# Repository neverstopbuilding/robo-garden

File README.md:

#RoboGarden

An open source garden hacking project. A robot that will take care of my plants, because I can't. 

Blog posts relating to the development of this project can be found at [http://neverstopbuilding.net/blog/categories/robo-garden](http://neverstopbuilding.net/blog/categories/robo-garden)

##License
<br /><span xmlns:dct="http://purl.org/dc/terms/" property="dct:title">RoboGarden</span> by <span xmlns:cc="http://creativecommons.org/ns#" property="cc:attributionName">Jason Fox</span> is licensed under a <a rel="license" href="http://creativecommons.org/licenses/by-nc-sa/3.0/deed.en_US">Creative Commons Attribution-NonCommercial-ShareAlike 3.0 Unported License</a>.

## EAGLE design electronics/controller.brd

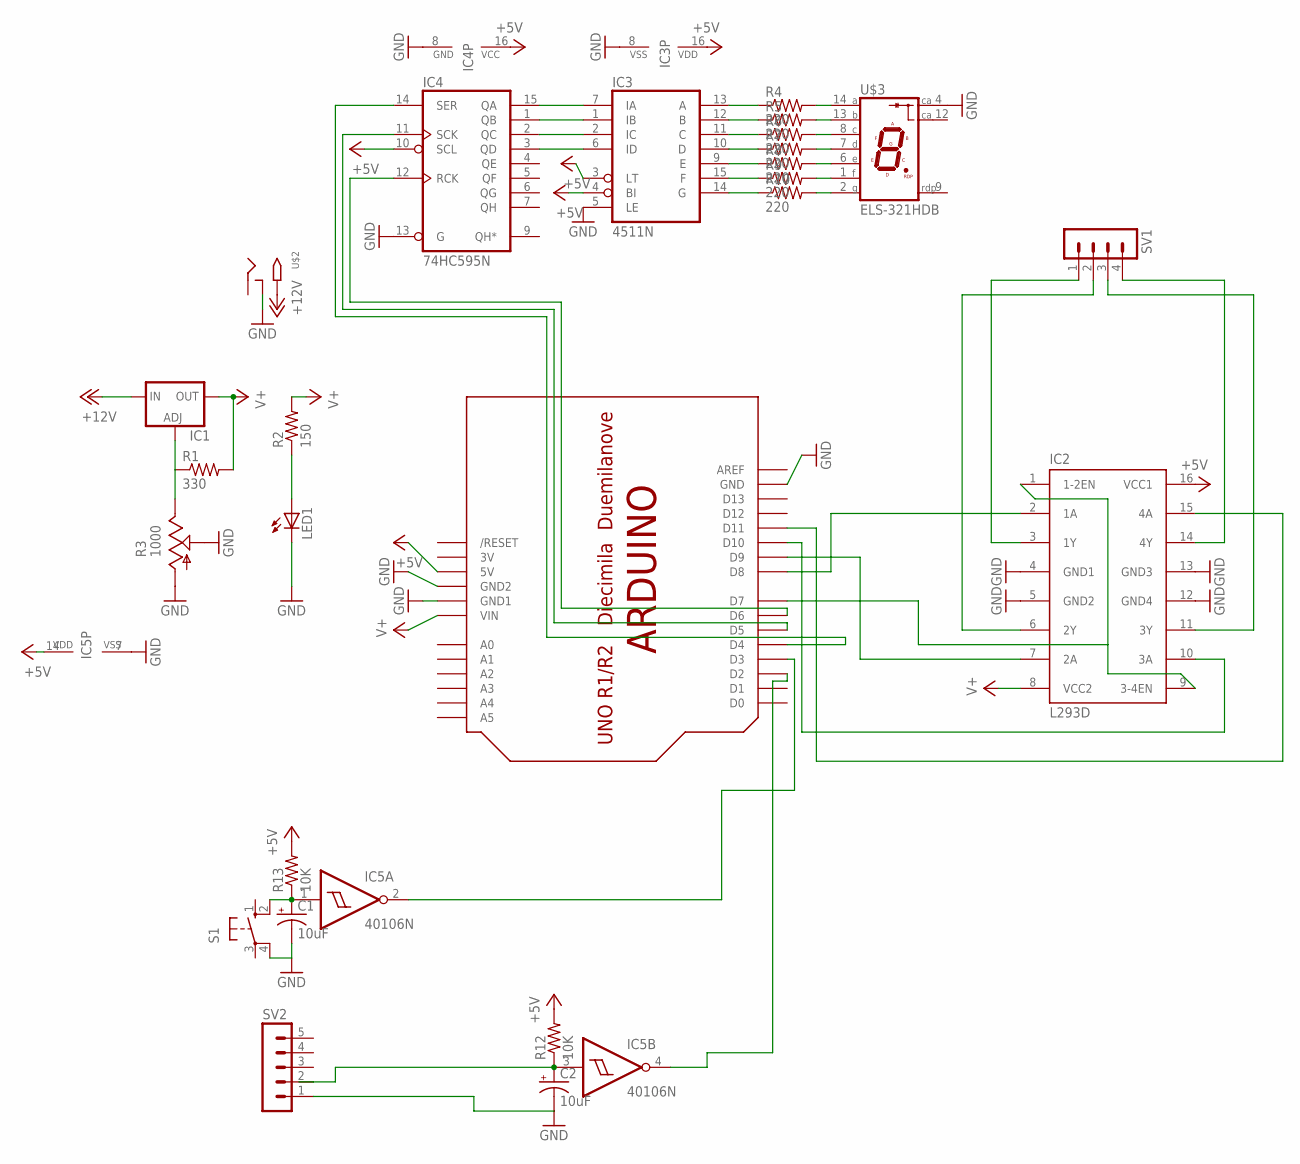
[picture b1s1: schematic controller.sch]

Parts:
C1, C2: 10uF; E2,5-5
IC1: LM317TS; 317TS
IC2: L293D; DIL16
IC3: 4511N; DIL16
IC4: 74HC595N; DIL16
IC5: 40106N; DIL14
LED1: LED5MM
R1: 330; 0207/10
R2: 150; 0207/10
R3: 1000; LI10
R4, R5, R6, R7, R8, R9, R10: 220; 0207/7
R12, R13: 10K; 0207/7
S1: 10-XX; B3F-10XX
SV1: MA04-1
SV2: MA05-1
U$1: ARDUINO-BPLACE
U$2: 2.1MMJACKTHM; PJ-102A
U$3: ELS-321HDB

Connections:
3V: U$1.3V
+5V: IC2.16 (VCC1), IC3.3 (LT), IC3.4 (BI), IC3.16 (VDD), IC4.10 (SCL), IC4.16 (VCC), IC5.14 (VDD), R12.2, R13.2, U$1.5V
+12V: IC1.3 (IN), U$2.TIP
GND: C1.-, C2.-, IC2.4 (GND1), IC2.5 (GND2), IC2.12 (GND4), IC2.13 (GND3), IC3.5 (LE), IC3.8 (VSS), IC4.8 (GND), IC4.13 (G), IC5.7 (VSS), LED1.K (C), R3.A, R3.S, S1.4 (P1), SV2.1, U$1.GND, U$1.GND1, U$1.GND2, U$2.RING_SW, U$3.4 (C)
unnamed: IC1.1 (ADJ), R1.1, R3.E
unnamed: IC3.13 (A), R4.1
unnamed: LED1.A, R2.1
unnamed: IC2.3 (1Y), SV1.1
unnamed: IC2.6 (2Y), SV1.2
unnamed: IC2.11 (3Y), SV1.3
unnamed: IC2.14 (4Y), SV1.4
unnamed: IC2.2 (1A), U$1.D8
unnamed: IC2.7 (2A), U$1.D9
unnamed: IC2.10 (3A), U$1.D10
unnamed: IC2.15 (4A), U$1.D11
unnamed: IC3.12 (B), R5.1
unnamed: IC2.1 (1-2EN), IC2.9 (3-4EN), U$1.D7
unnamed: IC3.11 (C), R6.1
unnamed: IC3.10 (D), R7.1
unnamed: IC3.9 (E), R8.1
unnamed: IC3.15 (F), R9.1
unnamed: IC3.14 (G), R10.1
unnamed: R4.2, U$3.14 (A)
unnamed: R5.2, U$3.13 (B)
unnamed: R6.2, U$3.8 (C)
unnamed: R7.2, U$3.7 (D)
unnamed: R8.2, U$3.6 (E)
unnamed: R9.2, U$3.1 (F)
unnamed: R10.2, U$3.2 (G)
unnamed: IC3.7 (IA), IC4.15 (QA)
unnamed: IC3.1 (IB), IC4.1 (QB)
unnamed: IC3.2 (IC), IC4.2 (QC)
unnamed: IC3.6 (ID), IC4.3 (QD)
unnamed: IC4.14 (SER), U$1.D4
unnamed: IC4.11 (SCK), U$1.D5
unnamed: IC4.12 (RCK), U$1.D6
unnamed: C1.+, IC5.1 (I), R13.1, S1.2 (S1)
unnamed: IC5.2 (O), U$1.D3
unnamed: C2.+, IC5.3 (I), R12.1, SV2.2
unnamed: IC5.4 (O), U$1.D2
V+: IC1.2 (OUT), IC2.8 (VCC2), R1.2, R2.2, U$1.VIN

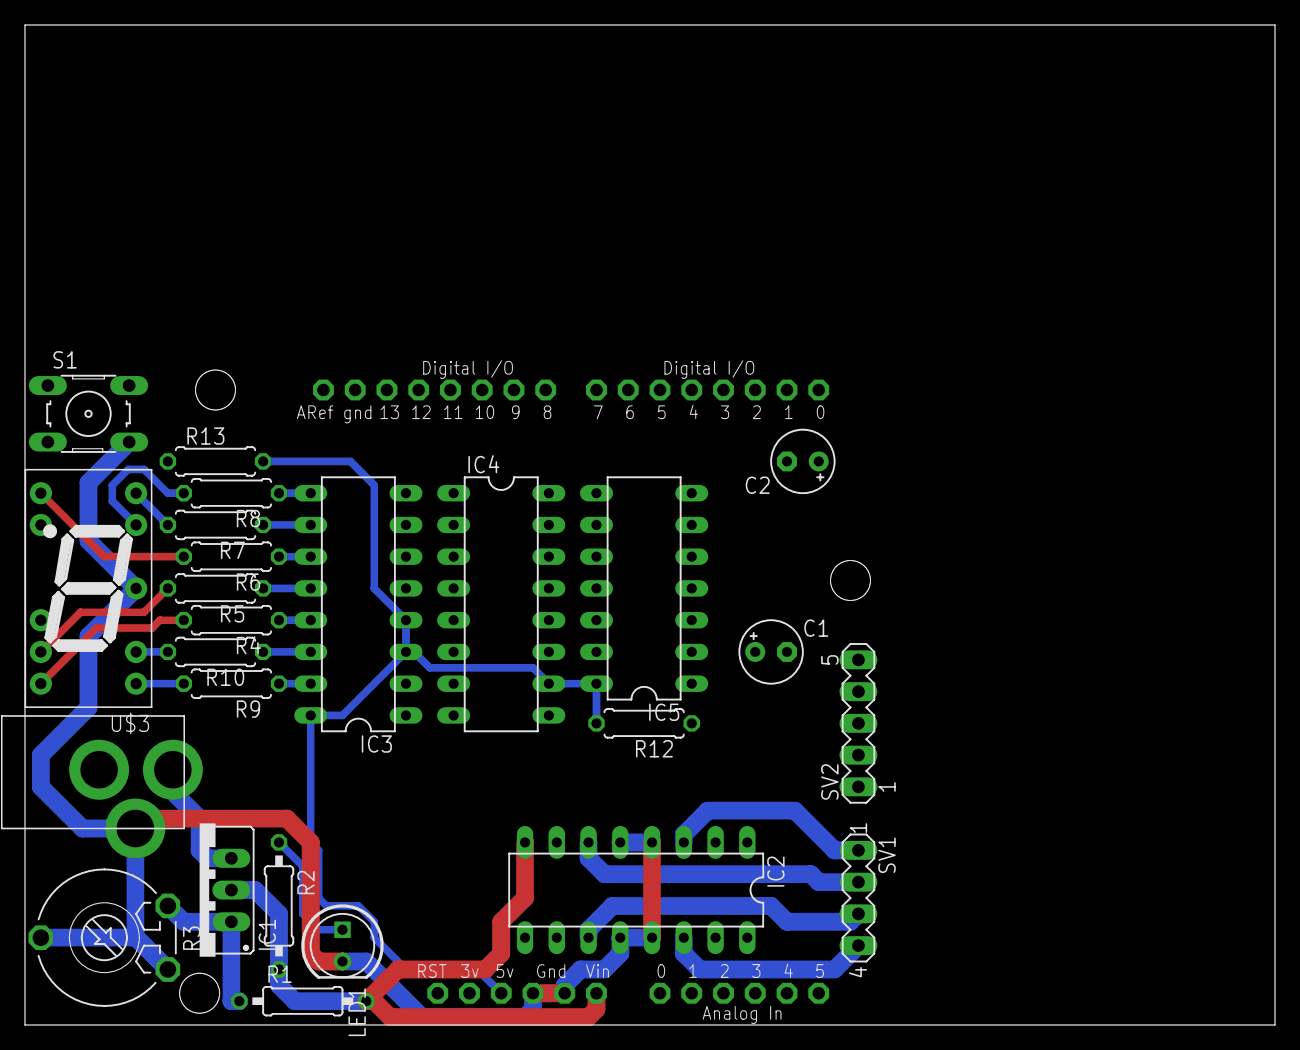
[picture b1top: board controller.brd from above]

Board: 2 copper layers, 100.0 x 80.0 mm, 26 parts (0 on the bottom side), 40 nets.

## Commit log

2013-10-13 added all the files to the repository
2013-10-13 added electronics files
2013-10-13 added CC license
2013-10-16 Updated #robogarden manual control code and schematic
2013-10-17 Updated #RoboGarden code with homing check, refactored the codebase to be cleaner with better comments and variable names, changed logic on button press
